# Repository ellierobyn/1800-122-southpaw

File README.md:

# 1800-122 Southpaw Keyboard [WIP]
A bigger than full size keyboard with the arrow keys compressed into the alphas like a 1800 and the number pad on the left (southpaw). Takes inspiration in name and form from the famous IBM Model F122.

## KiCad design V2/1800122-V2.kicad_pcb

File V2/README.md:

# 1800-122 Southpaw V2
This version of the board is the actively in development version using local repos and generally better best practices.

NOTE: The footprints used in the 122-LIB "SW_Hotswap_Kailh_MX_1.00u_**PnP**" & "SW_Hotswap_Kailh_MX_Plated_1.00u_**PnP**" are forked from the official KiCad key switch repo. Positionally they are the same to "SW_Hotswap_Kailh_MX_1.00u" & "SW_Hotswap_Kailh_MX_Plated_1.00u" **EXCEPT** their component origin is located in the same place as JLCPCB's PN C41430893 so the manufacturing files exported are compatible with their Pick and Place machines for automated PCB assembly. The 2 locating pin holes also had their nominal sizes shrunk by .001" to accommodate JLCPCB's capabilities.

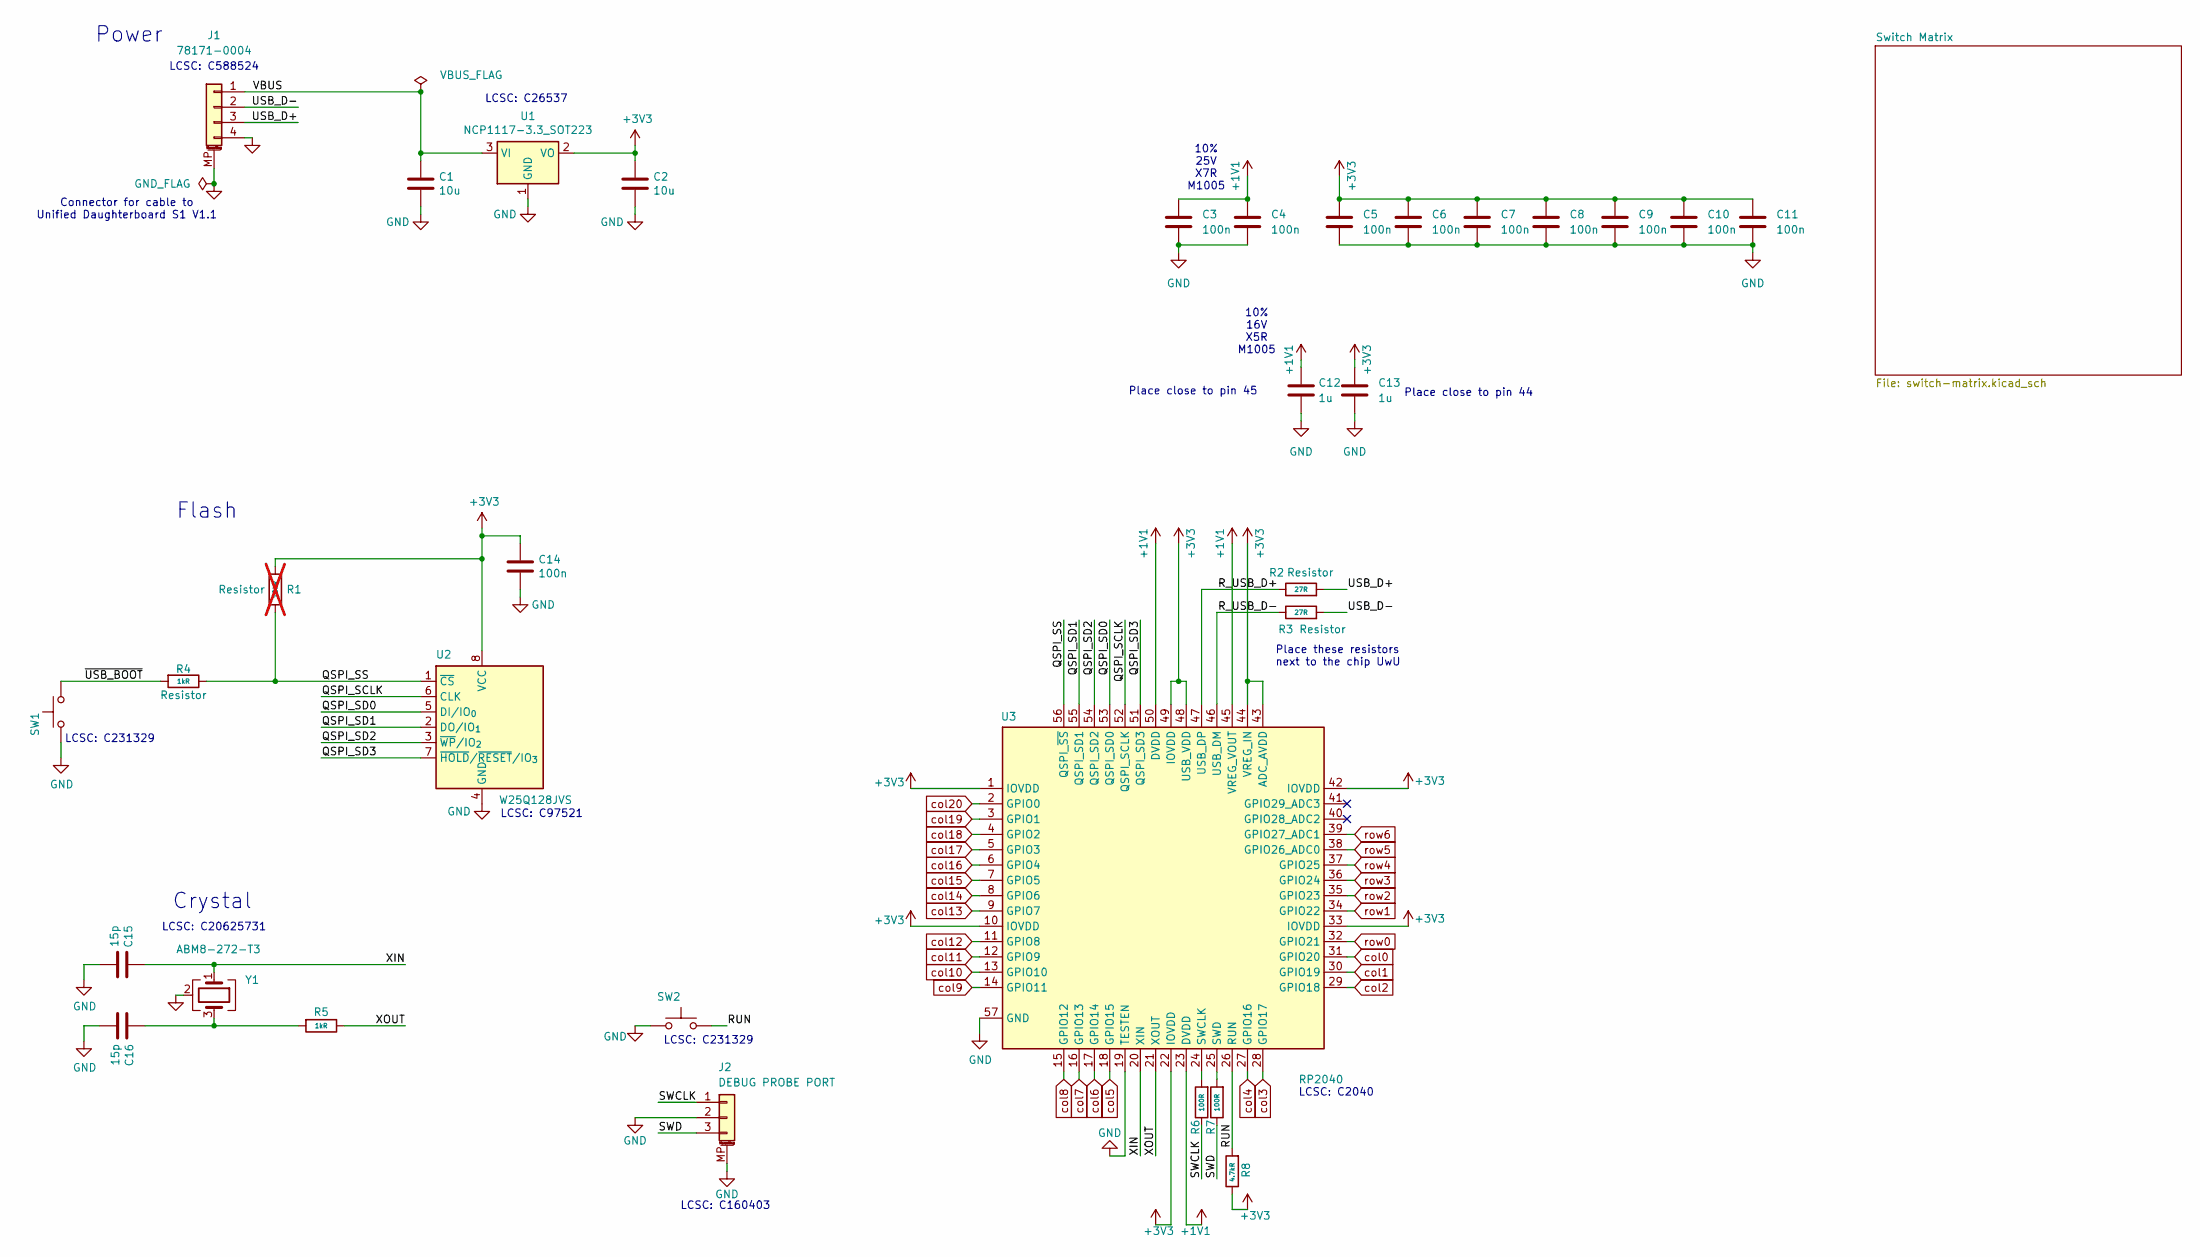
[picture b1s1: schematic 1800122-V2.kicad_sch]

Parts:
C1, C2: 10u; C_0402_1005Metric-JLCSILK
C3, C4, C5, C6, C7, C8, C9, C10, C11, C14: 100n; C_0402_1005Metric-JLCSILK
C12, C13: 1u; C_0402_1005Metric-JLCSILK
C15, C16: 15p; C_0402_1005Metric-JLCSILK
J1: 78171-0004; PicoEZMate-Reinforced-Lite; Manufacturer Part Number 78171-0004; LCSC Part Number C588524
J2: DEBUG PROBE PORT; JST_SH_SM03B-SRSS-TB_1x03-1MP_P1.00mm_Horizontal; LCSC Part Number C160403
R1: 10kR; R_0402_1005Metric-JLCSILK; not fitted
R2, R3: 27R; R_0402_1005Metric-JLCSILK
R4, R5: 1kR; R_0402_1005Metric-JLCSILK
R6, R7: 100R; R_0402_1005Metric-JLCSILK
R8: 4.7kR; R_0402_1005Metric-JLCSILK
SW1: BOOTSEL; SW_SPST_B3U-1000P; LCSC Part Number C231329
SW2: RESET; SW_SPST_B3U-1000P; LCSC Part Number C231329
U1: NCP1117-3.3_SOT223; SOT-223-3_TabPin2; LCSC Part Number C26537
U2: W25Q128JVS; SOIC-8_5.3x5.3mm_P1.27mm; LCSC Part Number C97521
U3: RP2040; part_uid RP-01EKHS-ZTKTEH; LCSC Part Number C2040
Y1: ABM8-272-T3; Crystal_SMD_3225-4Pin_3.2x2.5mm; LCSC Part Number C20625731

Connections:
+1V1: C3.1, C4.1, C12.1, U3.23 (DVDD), U3.45 (VREG_VOUT), U3.50 (DVDD)
+3V3: C2.1, C5.1, C6.1, C7.1, C8.1, C9.1, C10.1, C11.1, C13.1, C14.1, R1.1, R8.1, U1.2 (VO), U2.8 (VCC), U3.1 (IOVDD), U3.10 (IOVDD), U3.22 (IOVDD), U3.33 (IOVDD), U3.42 (IOVDD), U3.43 (ADC_AVDD), U3.44 (VREG_IN), U3.48 (USB_VDD), U3.49 (IOVDD)
/QSPI_SCLK: U2.6 (CLK), U3.52 (QSPI_SCLK)
/QSPI_SD0: U2.5 (DI/IO_{0}), U3.53 (QSPI_SD0)
/QSPI_SD1: U2.2 (DO/IO_{1}), U3.55 (QSPI_SD1)
/QSPI_SD2: U2.3 (~WP/IO_{2}), U3.54 (QSPI_SD2)
/QSPI_SD3: U2.7 (~HOLD/~RESET/IO_{3}), U3.51 (QSPI_SD3)
/QSPI_SS: R1.2, R4.1, U2.1 (~CS), U3.56 (QSPI_~SS)
/RUN: R8.2, SW2.2, U3.26 (RUN)
/R_USB_D+: R2.1, U3.47 (USB_DP)
/R_USB_D-: R3.1, U3.46 (USB_DM)
/SWCLK: J2.1, R6.1
/SWD: J2.3, R7.1
/USB_D+: J1.3, R2.2
/USB_D-: J1.2, R3.2
/VBUS: C1.1, J1.1, U1.3 (VI)
/XIN: C15.1, U3.20 (XIN), Y1.1
/XOUT: R5.1, U3.21 (XOUT)
/~USB_BOOT: R4.2, SW1.2
GND: C1.2, C2.2, C3.2, C4.2, C5.2, C6.2, C7.2, C8.2, C9.2, C10.2, C11.2, C12.2, C13.2, C14.2, C15.2, C16.2, J1.4, J1.MP (MountPin), J2.2, J2.MP (MountPin), SW1.1, SW2.1, U1.1 (GND), U2.4 (GND), U3.19 (TESTEN), U3.57 (GND), Y1.2 (G), Y1.4 (G)
unnamed: C16.1, R5.2, Y1.3
unnamed: R6.2, U3.24 (SWCLK)
unnamed: R7.2, U3.25 (SWD)
col0: U3.31 (GPIO20); also elsewhere on the board
col1: U3.30 (GPIO19); also elsewhere on the board
col2: U3.29 (GPIO18); also elsewhere on the board
col3: U3.28 (GPIO17); also elsewhere on the board
col4: U3.27 (GPIO16); also elsewhere on the board
col5: U3.18 (GPIO15); also elsewhere on the board
col6: U3.17 (GPIO14); also elsewhere on the board
col7: U3.16 (GPIO13); also elsewhere on the board
col8: U3.15 (GPIO12); also elsewhere on the board
col9: U3.14 (GPIO11); also elsewhere on the board
col10: U3.13 (GPIO10); also elsewhere on the board
col11: U3.12 (GPIO9); also elsewhere on the board
col12: U3.11 (GPIO8); also elsewhere on the board
col13: U3.9 (GPIO7); also elsewhere on the board
col14: U3.8 (GPIO6); also elsewhere on the board
col15: U3.7 (GPIO5); also elsewhere on the board
col16: U3.6 (GPIO4); also elsewhere on the board
col17: U3.5 (GPIO3); also elsewhere on the board
col18: U3.4 (GPIO2); also elsewhere on the board
col19: U3.3 (GPIO1); also elsewhere on the board
col20: U3.2 (GPIO0); also elsewhere on the board
row0: U3.32 (GPIO21); also elsewhere on the board
row1: U3.34 (GPIO22); also elsewhere on the board
row2: U3.35 (GPIO23); also elsewhere on the board
row3: U3.36 (GPIO24); also elsewhere on the board
row4: U3.37 (GPIO25); also elsewhere on the board
row5: U3.38 (GPIO26_ADC0); also elsewhere on the board
row6: U3.39 (GPIO27_ADC1); also elsewhere on the board

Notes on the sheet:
LCSC: C2040
LCSC: C20625731
LCSC: C26537
Power
Crystal
LCSC: C97521
Place close to pin 45
LCSC: C231329
Connector for cable to Unified Daughterboard S1 V1.1
10% 16V X5R M1005
LCSC: C160403
10% 25V X7R M1005
Place close to pin 44
LCSC: C588524
Place these resistors next to the chip UwU
Flash

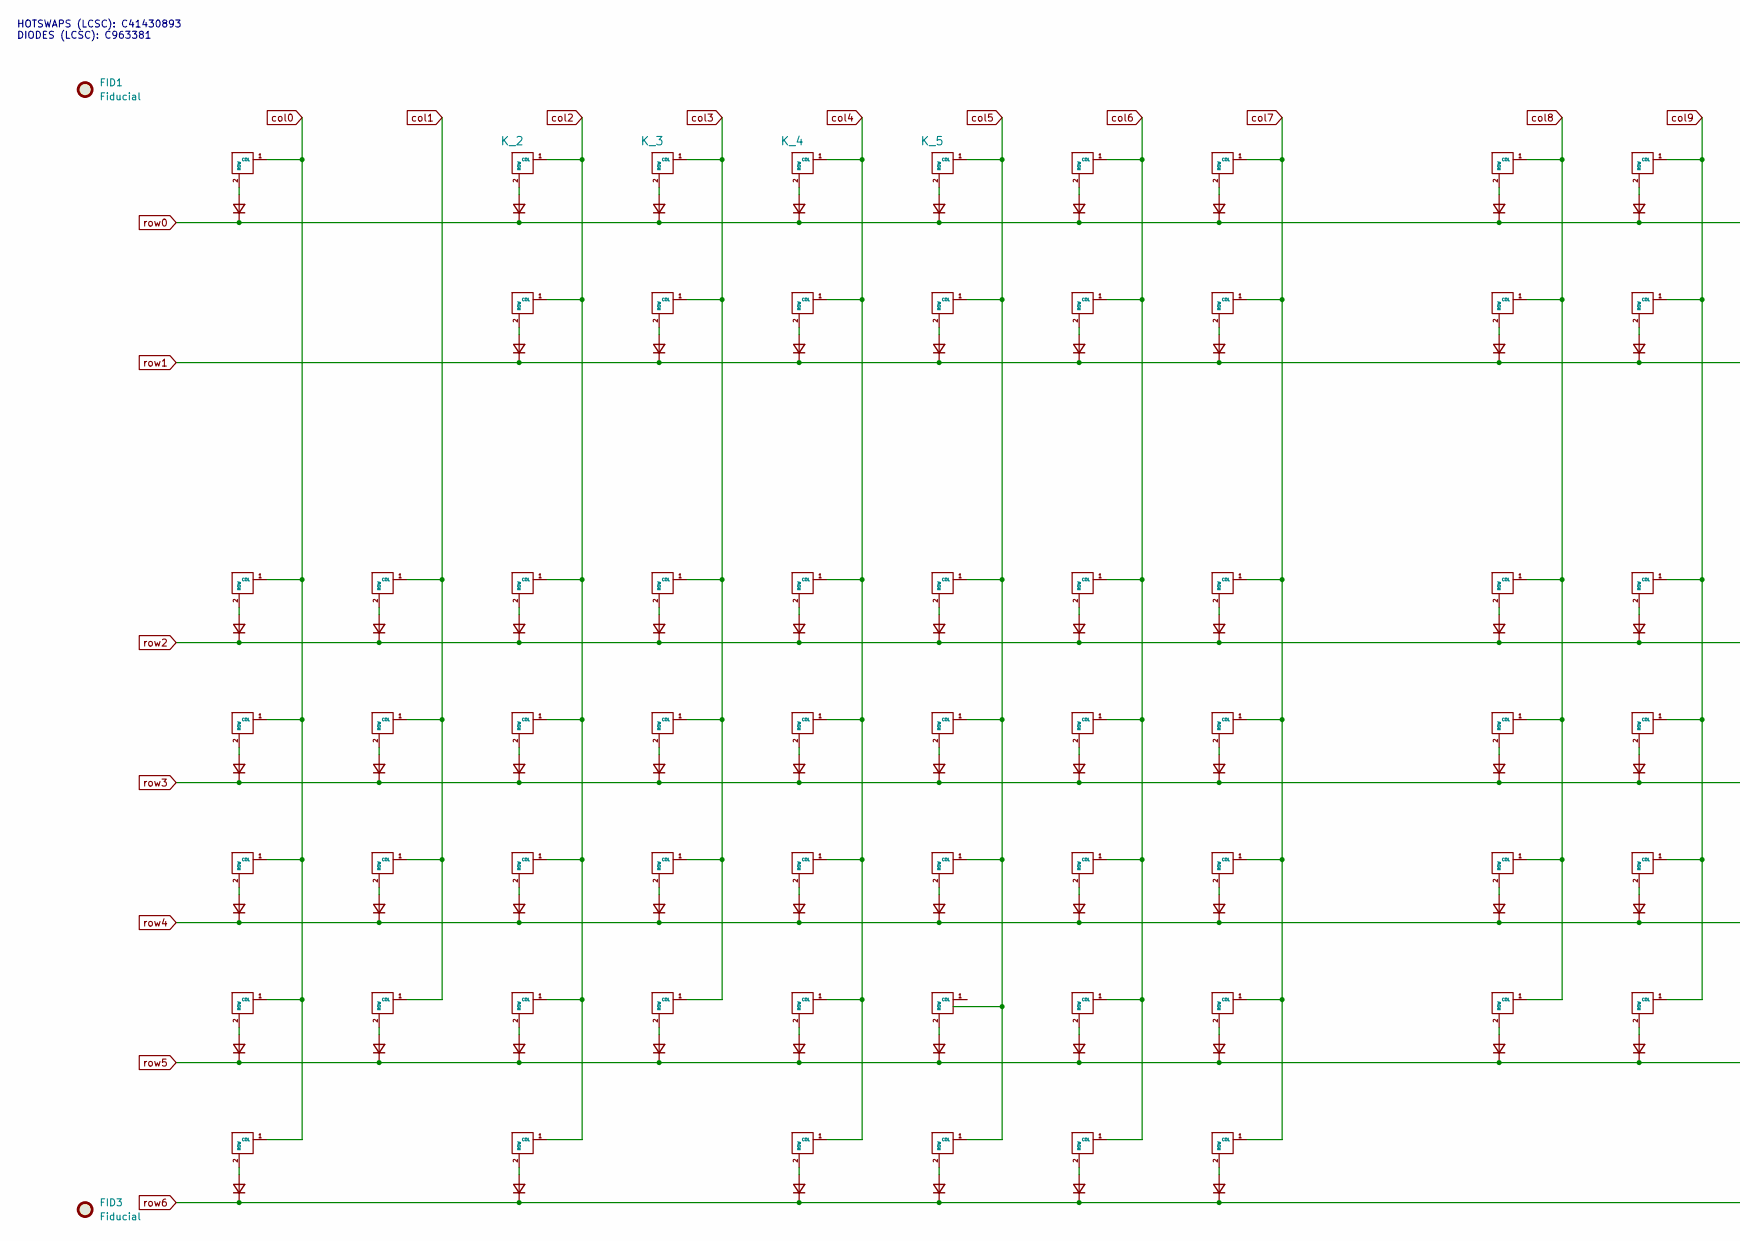
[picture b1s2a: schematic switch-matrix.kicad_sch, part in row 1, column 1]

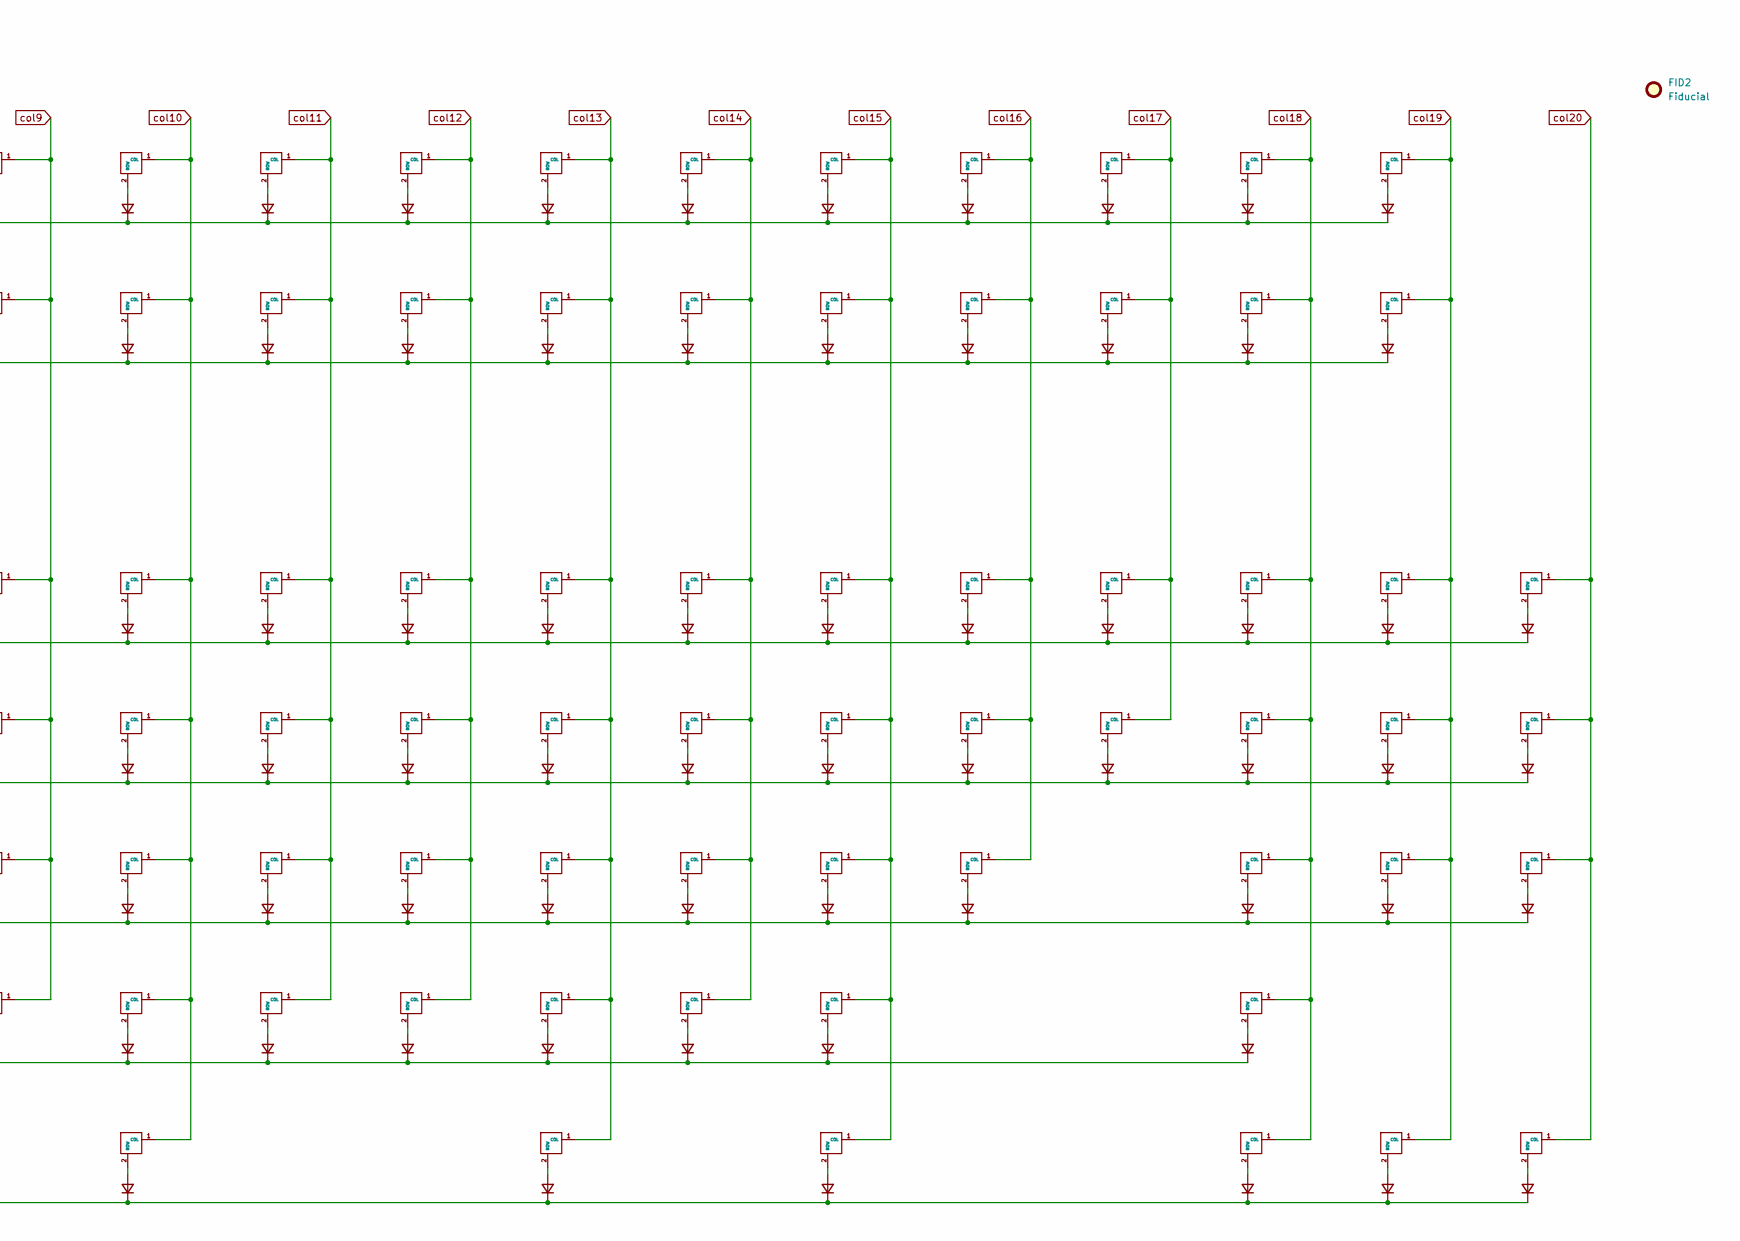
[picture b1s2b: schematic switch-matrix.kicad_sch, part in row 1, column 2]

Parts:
D_1, D_2, D_3, D_4, D_5, D_6, D_7, D_8, D_9, D_10, D_11, D_12, D_13, D_14, D_15, D_16, D_17, D_18, D_19, D_20, D_21, D_22, D_23, D_24, D_25, D_26, D_27, D_28, D_29, D_30, D_31, D_32, D_33, D_34, D_35, D_36, D_37, D_38, D_39, D_40, D_41, D_42, D_43, D_44, D_45, D_46, D_47, D_48, D_49, D_50, D_51, D_52, D_53, D_54, D_55, D_56, D_57, D_58, D_59, D_60, D_61, D_62, D_63, D_64, D_65, D_66, D_67, D_68, D_69, D_70, D_71, D_72, D_73, D_74, D_75, D_76, D_77, D_78, D_79, D_80, D_81, D_82, D_83, D_84, D_85, D_86, D_87, D_88, D_89, D_90, D_91, D_92, D_93, D_94, D_95, D_96, D_97, D_98, D_99, D_100, D_101, D_102, D_103, D_104, D_105, D_106, D_107, D_108, D_109, D_110, D_111, D_112, D_113, D_114, D_115, D_116, D_117, D_118, D_119, D_120, D_121, D_122, D_123, D_124, D_125, D_126, D_127, D_128: D; D_SOD-123; LCSC Part Number C963381
FID1, FID2, FID3: Fiducial; Fiducial_1mm_Mask2mm
K_1, K_2, K_3, K_4, K_5, K_6, K_7, K_8, K_9, K_10, K_11, K_12, K_13, K_14, K_15, K_16, K_17, K_18, K_19, K_20, K_21, K_22, K_23, K_24, K_25, K_26, K_27, K_28, K_29, K_30, K_31, K_32, K_33, K_34, K_35, K_36, K_37, K_38, K_39, K_40, K_41, K_42, K_43, K_44, K_45, K_46, K_47, K_48, K_49, K_50, K_51, K_52, K_53, K_54, K_55, K_56, K_57, K_58, K_59, K_60, K_61, K_62, K_63, K_64, K_65, K_66, K_67, K_68, K_69, K_70, K_71, K_72, K_73, K_74, K_75, K_76, K_77, K_78, K_79, K_80, K_81, K_82, K_83, K_84, K_85, K_86, K_87, K_88, K_89, K_90, K_91, K_92, K_93, K_94, K_95, K_96, K_97, K_98, K_99, K_100, K_101, K_102, K_103, K_104, K_105, K_106, K_107, K_108, K_109, K_110, K_111, K_112, K_113, K_114, K_115, K_116, K_117, K_118, K_119, K_120, K_121, K_122, K_123, K_124, K_125, K_126, K_127, K_128: KEYSW; SW_Hotswap_Kailh_MX_Plated_1.00u_PnP; LCSC Part Number C41430893

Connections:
unnamed: D_1.2 (A), K_1.2 (ROW)
unnamed: D_2.2 (A), K_2.2 (ROW)
unnamed: D_3.2 (A), K_3.2 (ROW)
unnamed: D_4.2 (A), K_4.2 (ROW)
unnamed: D_5.2 (A), K_5.2 (ROW)
unnamed: D_6.2 (A), K_6.2 (ROW)
unnamed: D_7.2 (A), K_7.2 (ROW)
unnamed: D_8.2 (A), K_8.2 (ROW)
unnamed: D_9.2 (A), K_9.2 (ROW)
unnamed: D_10.2 (A), K_10.2 (ROW)
unnamed: D_11.2 (A), K_11.2 (ROW)
unnamed: D_12.2 (A), K_12.2 (ROW)
unnamed: D_13.2 (A), K_13.2 (ROW)
unnamed: D_14.2 (A), K_14.2 (ROW)
unnamed: D_15.2 (A), K_15.2 (ROW)
unnamed: D_16.2 (A), K_16.2 (ROW)
unnamed: D_17.2 (A), K_17.2 (ROW)
unnamed: D_18.2 (A), K_18.2 (ROW)
unnamed: D_19.2 (A), K_19.2 (ROW)
unnamed: D_20.2 (A), K_20.2 (ROW)
unnamed: D_21.2 (A), K_21.2 (ROW)
unnamed: D_22.2 (A), K_22.2 (ROW)
unnamed: D_23.2 (A), K_23.2 (ROW)
unnamed: D_24.2 (A), K_24.2 (ROW)
unnamed: D_25.2 (A), K_25.2 (ROW)
unnamed: D_26.2 (A), K_26.2 (ROW)
unnamed: D_27.2 (A), K_27.2 (ROW)
unnamed: D_28.2 (A), K_28.2 (ROW)
unnamed: D_29.2 (A), K_29.2 (ROW)
unnamed: D_30.2 (A), K_30.2 (ROW)
unnamed: D_31.2 (A), K_31.2 (ROW)
unnamed: D_32.2 (A), K_32.2 (ROW)
unnamed: D_33.2 (A), K_33.2 (ROW)
unnamed: D_34.2 (A), K_34.2 (ROW)
unnamed: D_35.2 (A), K_35.2 (ROW)
unnamed: D_36.2 (A), K_36.2 (ROW)
unnamed: D_37.2 (A), K_37.2 (ROW)
unnamed: D_38.2 (A), K_38.2 (ROW)
unnamed: D_39.2 (A), K_39.2 (ROW)
unnamed: D_40.2 (A), K_40.2 (ROW)
unnamed: D_41.2 (A), K_41.2 (ROW)
unnamed: D_42.2 (A), K_42.2 (ROW)
unnamed: D_43.2 (A), K_43.2 (ROW)
unnamed: D_44.2 (A), K_44.2 (ROW)
unnamed: D_45.2 (A), K_45.2 (ROW)
unnamed: D_46.2 (A), K_46.2 (ROW)
unnamed: D_47.2 (A), K_47.2 (ROW)
unnamed: D_48.2 (A), K_48.2 (ROW)
unnamed: D_49.2 (A), K_49.2 (ROW)
unnamed: D_50.2 (A), K_50.2 (ROW)
unnamed: D_51.2 (A), K_51.2 (ROW)
unnamed: D_52.2 (A), K_52.2 (ROW)
unnamed: D_53.2 (A), K_53.2 (ROW)
unnamed: D_54.2 (A), K_54.2 (ROW)
unnamed: D_55.2 (A), K_55.2 (ROW)
unnamed: D_56.2 (A), K_56.2 (ROW)
unnamed: D_57.2 (A), K_57.2 (ROW)
unnamed: D_58.2 (A), K_58.2 (ROW)
unnamed: D_59.2 (A), K_59.2 (ROW)
unnamed: D_60.2 (A), K_60.2 (ROW)
unnamed: D_61.2 (A), K_61.2 (ROW)
unnamed: D_62.2 (A), K_62.2 (ROW)
unnamed: D_63.2 (A), K_63.2 (ROW)
unnamed: D_64.2 (A), K_64.2 (ROW)
unnamed: D_65.2 (A), K_65.2 (ROW)
unnamed: D_66.2 (A), K_66.2 (ROW)
unnamed: D_67.2 (A), K_67.2 (ROW)
unnamed: D_68.2 (A), K_68.2 (ROW)
unnamed: D_69.2 (A), K_69.2 (ROW)
unnamed: D_70.2 (A), K_70.2 (ROW)
unnamed: D_71.2 (A), K_71.2 (ROW)
unnamed: D_72.2 (A), K_72.2 (ROW)
unnamed: D_73.2 (A), K_73.2 (ROW)
unnamed: D_74.2 (A), K_74.2 (ROW)
unnamed: D_75.2 (A), K_75.2 (ROW)
unnamed: D_76.2 (A), K_76.2 (ROW)
unnamed: D_77.2 (A), K_77.2 (ROW)
unnamed: D_78.2 (A), K_78.2 (ROW)
unnamed: D_79.2 (A), K_79.2 (ROW)
unnamed: D_80.2 (A), K_80.2 (ROW)
unnamed: D_81.2 (A), K_81.2 (ROW)
unnamed: D_82.2 (A), K_82.2 (ROW)
unnamed: D_83.2 (A), K_83.2 (ROW)
unnamed: D_84.2 (A), K_84.2 (ROW)
unnamed: D_85.2 (A), K_85.2 (ROW)
unnamed: D_86.2 (A), K_86.2 (ROW)
unnamed: D_87.2 (A), K_87.2 (ROW)
unnamed: D_88.2 (A), K_88.2 (ROW)
unnamed: D_89.2 (A), K_89.2 (ROW)
unnamed: D_90.2 (A), K_90.2 (ROW)
unnamed: D_91.2 (A), K_91.2 (ROW)
unnamed: D_92.2 (A), K_92.2 (ROW)
unnamed: D_93.2 (A), K_93.2 (ROW)
unnamed: D_94.2 (A), K_94.2 (ROW)
unnamed: D_95.2 (A), K_95.2 (ROW)
unnamed: D_96.2 (A), K_96.2 (ROW)
unnamed: D_97.2 (A), K_97.2 (ROW)
unnamed: D_98.2 (A), K_98.2 (ROW)
unnamed: D_99.2 (A), K_99.2 (ROW)
unnamed: D_100.2 (A), K_100.2 (ROW)
unnamed: D_101.2 (A), K_101.2 (ROW)
unnamed: D_102.2 (A), K_102.2 (ROW)
unnamed: D_103.2 (A), K_103.2 (ROW)
unnamed: D_104.2 (A), K_104.2 (ROW)
unnamed: D_105.2 (A), K_105.2 (ROW_2)
unnamed: D_106.2 (A), K_106.2 (ROW)
unnamed: D_107.2 (A), K_107.2 (ROW)
unnamed: D_108.2 (A), K_108.2 (ROW)
unnamed: D_109.2 (A), K_109.2 (ROW)
unnamed: D_110.2 (A), K_110.2 (ROW)
unnamed: D_111.2 (A), K_111.2 (ROW)
unnamed: D_112.2 (A), K_112.2 (ROW)
unnamed: D_113.2 (A), K_113.2 (ROW)
unnamed: D_114.2 (A), K_114.2 (ROW)
unnamed: D_115.2 (A), K_115.2 (ROW)
unnamed: D_116.2 (A), K_116.2 (ROW)
unnamed: D_117.2 (A), K_117.2 (ROW)
unnamed: D_118.2 (A), K_118.2 (ROW)
unnamed: D_119.2 (A), K_119.2 (ROW)
unnamed: D_120.2 (A), K_120.2 (ROW)
unnamed: D_121.2 (A), K_121.2 (ROW)
unnamed: D_122.2 (A), K_122.2 (ROW)
unnamed: D_123.2 (A), K_123.2 (ROW)
unnamed: D_124.2 (A), K_124.2 (ROW)
unnamed: D_125.2 (A), K_125.2 (ROW)
unnamed: D_126.2 (A), K_126.2 (ROW)
unnamed: D_127.2 (A), K_127.2 (ROW)
unnamed: D_128.2 (A), K_128.2 (ROW)
col0: K_1.1 (COL), K_38.1 (COL), K_59.1 (COL), K_80.1 (COL), K_100.1 (COL), K_117.1 (COL); also elsewhere on the board
col1: K_39.1 (COL), K_60.1 (COL), K_81.1 (COL), K_101.1 (COL); also elsewhere on the board
col2: K_2.1 (COL), K_20.1 (COL), K_40.1 (COL), K_61.1 (COL), K_82.1 (COL), K_102.1 (COL), K_118.1 (COL); also elsewhere on the board
col3: K_3.1 (COL), K_21.1 (COL), K_41.1 (COL), K_62.1 (COL), K_83.1 (COL), K_103.1 (COL); also elsewhere on the board
col4: K_4.1 (COL), K_22.1 (COL), K_42.1 (COL), K_63.1 (COL), K_84.1 (COL), K_104.1 (COL), K_119.1 (COL); also elsewhere on the board
col5: K_5.1 (COL), K_23.1 (COL), K_43.1 (COL), K_64.1 (COL), K_85.1 (COL), K_120.1 (COL); also elsewhere on the board
col6: K_6.1 (COL), K_24.1 (COL), K_44.1 (COL), K_65.1 (COL), K_86.1 (COL), K_106.1 (COL), K_121.1 (COL); also elsewhere on the board
col7: K_7.1 (COL), K_25.1 (COL), K_45.1 (COL), K_66.1 (COL), K_87.1 (COL), K_107.1 (COL), K_122.1 (COL); also elsewhere on the board
col8: K_8.1 (COL), K_26.1 (COL), K_46.1 (COL), K_67.1 (COL), K_88.1 (COL), K_108.1 (COL); also elsewhere on the board
col9: K_9.1 (COL), K_27.1 (COL), K_47.1 (COL), K_68.1 (COL), K_89.1 (COL), K_109.1 (COL); also elsewhere on the board
col10: K_10.1 (COL), K_28.1 (COL), K_48.1 (COL), K_69.1 (COL), K_90.1 (COL), K_110.1 (COL), K_123.1 (COL); also elsewhere on the board
col11: K_11.1 (COL), K_29.1 (COL), K_49.1 (COL), K_70.1 (COL), K_91.1 (COL), K_111.1 (COL); also elsewhere on the board
col12: K_12.1 (COL), K_30.1 (COL), K_50.1 (COL), K_71.1 (COL), K_92.1 (COL), K_112.1 (COL); also elsewhere on the board
col13: K_13.1 (COL), K_31.1 (COL), K_51.1 (COL), K_72.1 (COL), K_93.1 (COL), K_113.1 (COL), K_124.1 (COL); also elsewhere on the board
col14: K_14.1 (COL), K_32.1 (COL), K_52.1 (COL), K_73.1 (COL), K_94.1 (COL), K_114.1 (COL); also elsewhere on the board
col15: K_15.1 (COL), K_33.1 (COL), K_53.1 (COL), K_74.1 (COL), K_95.1 (COL), K_115.1 (COL), K_125.1 (COL); also elsewhere on the board
col16: K_16.1 (COL), K_34.1 (COL), K_54.1 (COL), K_75.1 (COL), K_96.1 (COL); also elsewhere on the board
col17: K_17.1 (COL), K_35.1 (COL), K_55.1 (COL), K_76.1 (COL); also elsewhere on the board
col18: K_18.1 (COL), K_36.1 (COL), K_56.1 (COL), K_77.1 (COL), K_97.1 (COL), K_116.1 (COL), K_126.1 (COL); also elsewhere on the board
col19: K_19.1 (COL), K_37.1 (COL), K_57.1 (COL), K_78.1 (COL), K_98.1 (COL), K_127.1 (COL); also elsewhere on the board
col20: K_58.1 (COL), K_79.1 (COL), K_99.1 (COL), K_128.1 (COL); also elsewhere on the board
row0: D_1.1 (K), D_2.1 (K), D_3.1 (K), D_4.1 (K), D_5.1 (K), D_6.1 (K), D_7.1 (K), D_8.1 (K), D_9.1 (K), D_10.1 (K), D_11.1 (K), D_12.1 (K), D_13.1 (K), D_14.1 (K), D_15.1 (K), D_16.1 (K), D_17.1 (K), D_18.1 (K), D_19.1 (K); also elsewhere on the board
row1: D_20.1 (K), D_21.1 (K), D_22.1 (K), D_23.1 (K), D_24.1 (K), D_25.1 (K), D_26.1 (K), D_27.1 (K), D_28.1 (K), D_29.1 (K), D_30.1 (K), D_31.1 (K), D_32.1 (K), D_33.1 (K), D_34.1 (K), D_35.1 (K), D_36.1 (K), D_37.1 (K); also elsewhere on the board
row2: D_38.1 (K), D_39.1 (K), D_40.1 (K), D_41.1 (K), D_42.1 (K), D_43.1 (K), D_44.1 (K), D_45.1 (K), D_46.1 (K), D_47.1 (K), D_48.1 (K), D_49.1 (K), D_50.1 (K), D_51.1 (K), D_52.1 (K), D_53.1 (K), D_54.1 (K), D_55.1 (K), D_56.1 (K), D_57.1 (K), D_58.1 (K); also elsewhere on the board
row3: D_59.1 (K), D_60.1 (K), D_61.1 (K), D_62.1 (K), D_63.1 (K), D_64.1 (K), D_65.1 (K), D_66.1 (K), D_67.1 (K), D_68.1 (K), D_69.1 (K), D_70.1 (K), D_71.1 (K), D_72.1 (K), D_73.1 (K), D_74.1 (K), D_75.1 (K), D_76.1 (K), D_77.1 (K), D_78.1 (K), D_79.1 (K); also elsewhere on the board
row4: D_80.1 (K), D_81.1 (K), D_82.1 (K), D_83.1 (K), D_84.1 (K), D_85.1 (K), D_86.1 (K), D_87.1 (K), D_88.1 (K), D_89.1 (K), D_90.1 (K), D_91.1 (K), D_92.1 (K), D_93.1 (K), D_94.1 (K), D_95.1 (K), D_96.1 (K), D_97.1 (K), D_98.1 (K), D_99.1 (K); also elsewhere on the board
row5: D_100.1 (K), D_101.1 (K), D_102.1 (K), D_103.1 (K), D_104.1 (K), D_105.1 (K), D_106.1 (K), D_107.1 (K), D_108.1 (K), D_109.1 (K), D_110.1 (K), D_111.1 (K), D_112.1 (K), D_113.1 (K), D_114.1 (K), D_115.1 (K), D_116.1 (K); also elsewhere on the board
row6: D_117.1 (K), D_118.1 (K), D_119.1 (K), D_120.1 (K), D_121.1 (K), D_122.1 (K), D_123.1 (K), D_124.1 (K), D_125.1 (K), D_126.1 (K), D_127.1 (K), D_128.1 (K); also elsewhere on the board

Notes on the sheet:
HOTSWAPS (LCSC): C41430893 DIODES (LCSC): C963381

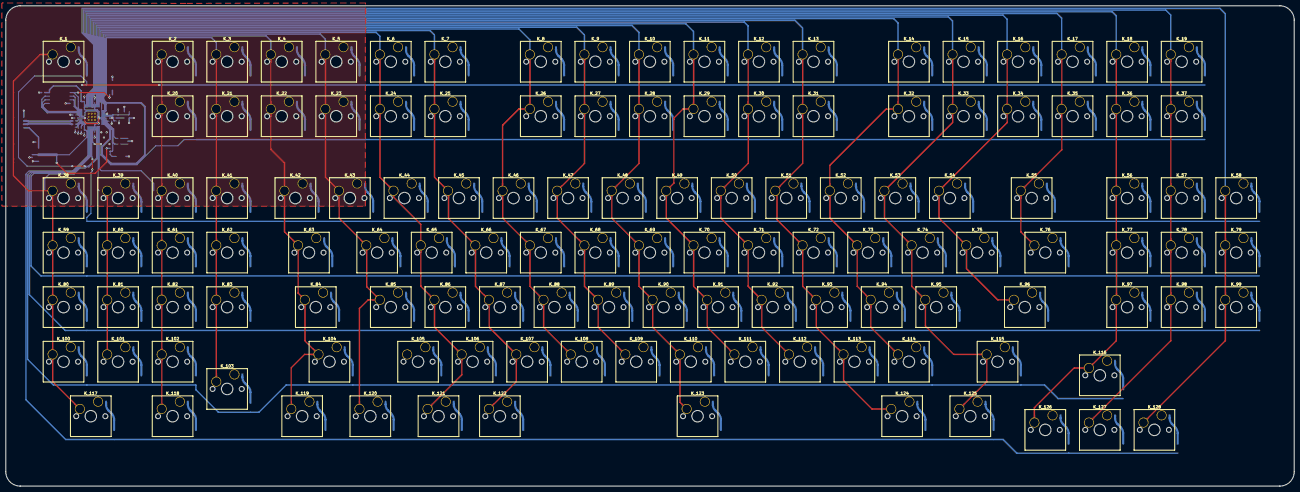
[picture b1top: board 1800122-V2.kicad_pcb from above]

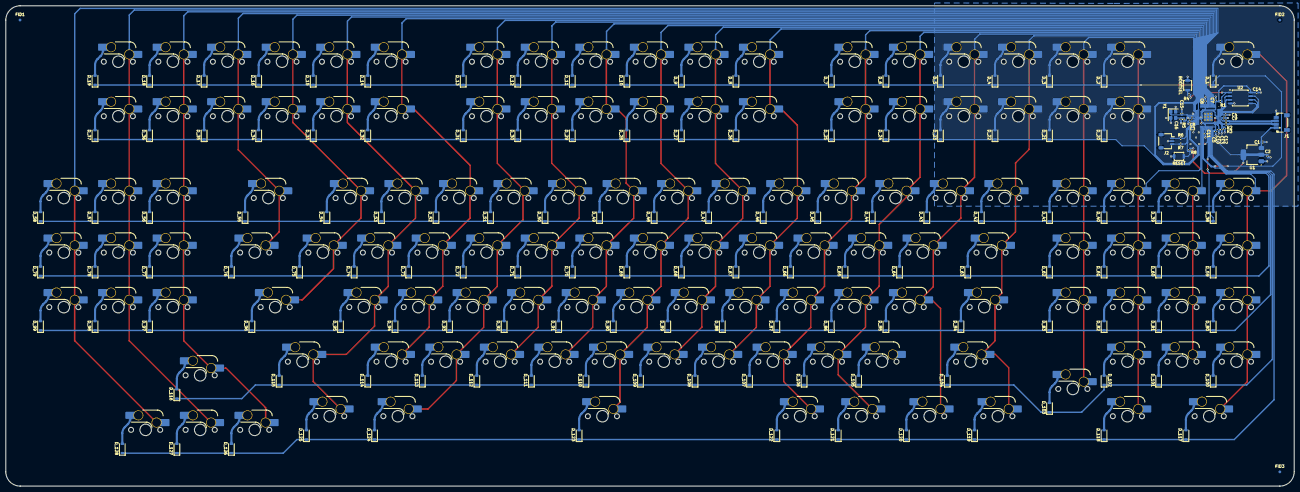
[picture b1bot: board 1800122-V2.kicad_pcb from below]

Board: 2 copper layers, 450.0 x 167.8 mm, 291 parts (163 on the bottom side), 179 nets.

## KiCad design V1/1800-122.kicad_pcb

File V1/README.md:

# NOTICE: DEPRECATED

This version of the PCB utilized ai03's deprecated MX Keyswitch Libraries, a random RP2040 lib and a random W25Q128JVSIQ lib. I don't recommend using this PCB as a finished project but may be a helpful reference. This PCB was never manufactured so there are also probably DRC errors.

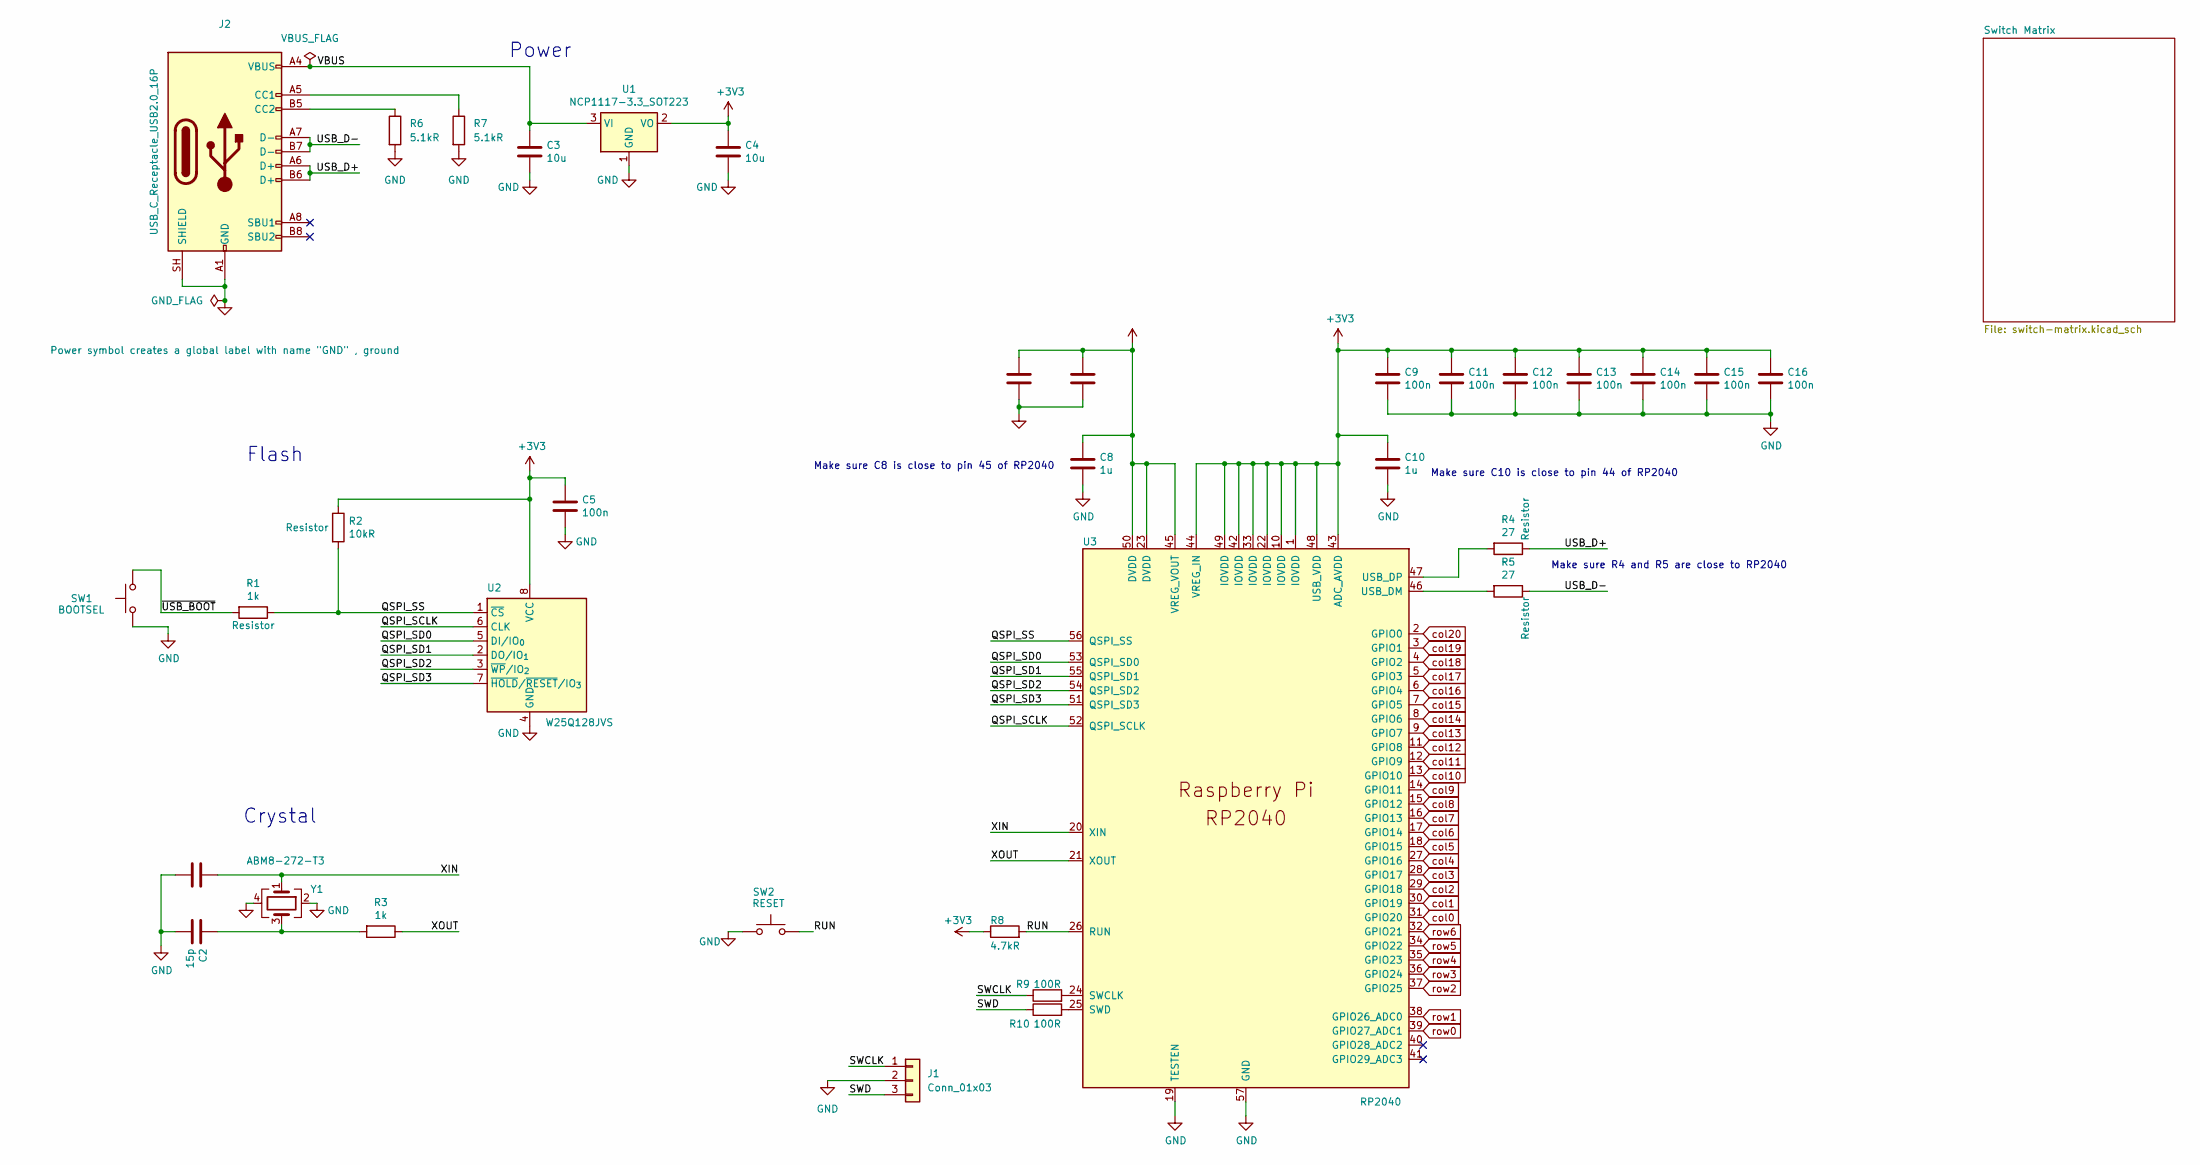
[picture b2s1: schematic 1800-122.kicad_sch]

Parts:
C1, C2: 15p; C_0402_1005Metric_Pad0.74x0.62mm_HandSolder
C3, C4: 10u; C_0402_1005Metric_Pad0.74x0.62mm_HandSolder
C5, C6, C7, C9, C11, C12, C13, C14, C15, C16: 100n; C_0402_1005Metric_Pad0.74x0.62mm_HandSolder
C8, C10: 1u; C_0402_1005Metric_Pad0.74x0.62mm_HandSolder
J1: Conn_01x03; JST_SH_SM03B-SRSS-TB_1x03-1MP_P1.00mm_Horizontal
J2: USB_C_Receptacle_USB2.0_16P; USB_C_Receptacle_GCT_USB4105-xx-A_16P_TopMnt_Horizontal
R1, R3: 1k; R_0402_1005Metric_Pad0.72x0.64mm_HandSolder
R2: 10kR; R_0402_1005Metric_Pad0.72x0.64mm_HandSolder
R4, R5: 27; R_0402_1005Metric_Pad0.72x0.64mm_HandSolder
R6, R7: 5.1kR; R_0402_1005Metric_Pad0.72x0.64mm_HandSolder
R8: 4.7kR; R_0402_1005Metric_Pad0.72x0.64mm_HandSolder
R9, R10: 100R; R_0402_1005Metric_Pad0.72x0.64mm_HandSolder
SW1: BOOTSEL; SW_SPST_PTS810
SW2: RESET; SW_SPST_PTS810
U1: NCP1117-3.3_SOT223; SOT-223-3_TabPin2
U2: W25Q128JVS; SOIC-8_5.3x5.3mm_P1.27mm
U3: RP2040; RP2040-QFN-56
Y1: ABM8-272-T3; Crystal_SMD_3225-4Pin_3.2x2.5mm

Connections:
+1V1: C6.1, C7.1, C8.1, U3.23 (DVDD), U3.45 (VREG_VOUT), U3.50 (DVDD)
+3V3: C4.1, C5.1, C9.1, C10.1, C11.1, C12.1, C13.1, C14.1, C15.1, C16.1, R2.1, R8.1, U1.2 (VO), U2.8 (VCC), U3.1 (IOVDD), U3.10 (IOVDD), U3.22 (IOVDD), U3.33 (IOVDD), U3.42 (IOVDD), U3.43 (ADC_AVDD), U3.44 (VREG_IN), U3.48 (USB_VDD), U3.49 (IOVDD)
/QSPI_SCLK: U2.6 (CLK), U3.52 (QSPI_SCLK)
/QSPI_SD0: U2.5 (DI/IO_{0}), U3.53 (QSPI_SD0)
/QSPI_SD1: U2.2 (DO/IO_{1}), U3.55 (QSPI_SD1)
/QSPI_SD2: U2.3 (~WP/IO_{2}), U3.54 (QSPI_SD2)
/QSPI_SD3: U2.7 (~HOLD/~RESET/IO_{3}), U3.51 (QSPI_SD3)
/QSPI_SS: R1.1, R2.2, U2.1 (~CS), U3.56 (QSPI_SS)
/RUN: R8.2, SW2.2, U3.26 (RUN)
/SWCLK: J1.1, R9.1
/SWD: J1.3, R10.1
/USB_D+: J2.A6 (D+), J2.B6 (D+), R4.1
/USB_D-: J2.A7 (D-), J2.B7 (D-), R5.1
/VBUS: C3.1, J2.A4 (VBUS), J2.A9 (VBUS), J2.B4 (VBUS), J2.B9 (VBUS), U1.3 (VI)
/XIN: C1.1, U3.20 (XIN), Y1.1
/XOUT: R3.1, U3.21 (XOUT)
/~USB_BOOT: R1.2, SW1.2
GND: C1.2, C2.2, C3.2, C4.2, C5.2, C6.2, C7.2, C8.2, C9.2, C10.2, C11.2, C12.2, C13.2, C14.2, C15.2, C16.2, J1.2, J2.A1 (GND), J2.A12 (GND), J2.B1 (GND), J2.B12 (GND), J2.SH (SHIELD), R6.2, R7.2, SW1.1, SW2.1, U1.1 (GND), U2.4 (GND), U3.19 (TESTEN), U3.57 (GND), Y1.2, Y1.4
unnamed: C2.1, R3.2, Y1.3
unnamed: J2.A5 (CC1), R7.1
unnamed: J2.B5 (CC2), R6.1
unnamed: R9.2, U3.24 (SWCLK)
unnamed: R10.2, U3.25 (SWD)
unnamed: R5.2, U3.46 (USB_DM)
unnamed: R4.2, U3.47 (USB_DP)
col0: U3.31 (GPIO20); also elsewhere on the board
col1: U3.30 (GPIO19); also elsewhere on the board
col2: U3.29 (GPIO18); also elsewhere on the board
col3: U3.28 (GPIO17); also elsewhere on the board
col4: U3.27 (GPIO16); also elsewhere on the board
col5: U3.18 (GPIO15); also elsewhere on the board
col6: U3.17 (GPIO14); also elsewhere on the board
col7: U3.16 (GPIO13); also elsewhere on the board
col8: U3.15 (GPIO12); also elsewhere on the board
col9: U3.14 (GPIO11); also elsewhere on the board
col10: U3.13 (GPIO10); also elsewhere on the board
col11: U3.12 (GPIO9); also elsewhere on the board
col12: U3.11 (GPIO8); also elsewhere on the board
col13: U3.9 (GPIO7); also elsewhere on the board
col14: U3.8 (GPIO6); also elsewhere on the board
col15: U3.7 (GPIO5); also elsewhere on the board
col16: U3.6 (GPIO4); also elsewhere on the board
col17: U3.5 (GPIO3); also elsewhere on the board
col18: U3.4 (GPIO2); also elsewhere on the board
col19: U3.3 (GPIO1); also elsewhere on the board
col20: U3.2 (GPIO0); also elsewhere on the board
row0: U3.39 (GPIO27_ADC1); also elsewhere on the board
row1: U3.38 (GPIO26_ADC0); also elsewhere on the board
row2: U3.37 (GPIO25); also elsewhere on the board
row3: U3.36 (GPIO24); also elsewhere on the board
row4: U3.35 (GPIO23); also elsewhere on the board
row5: U3.34 (GPIO22); also elsewhere on the board
row6: U3.32 (GPIO21); also elsewhere on the board

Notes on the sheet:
Power
Crystal
Make sure C8 is close to pin 45 of RP2040
Make sure C10 is close to pin 44 of RP2040
Make sure R4 and R5 are close to RP2040
Flash
